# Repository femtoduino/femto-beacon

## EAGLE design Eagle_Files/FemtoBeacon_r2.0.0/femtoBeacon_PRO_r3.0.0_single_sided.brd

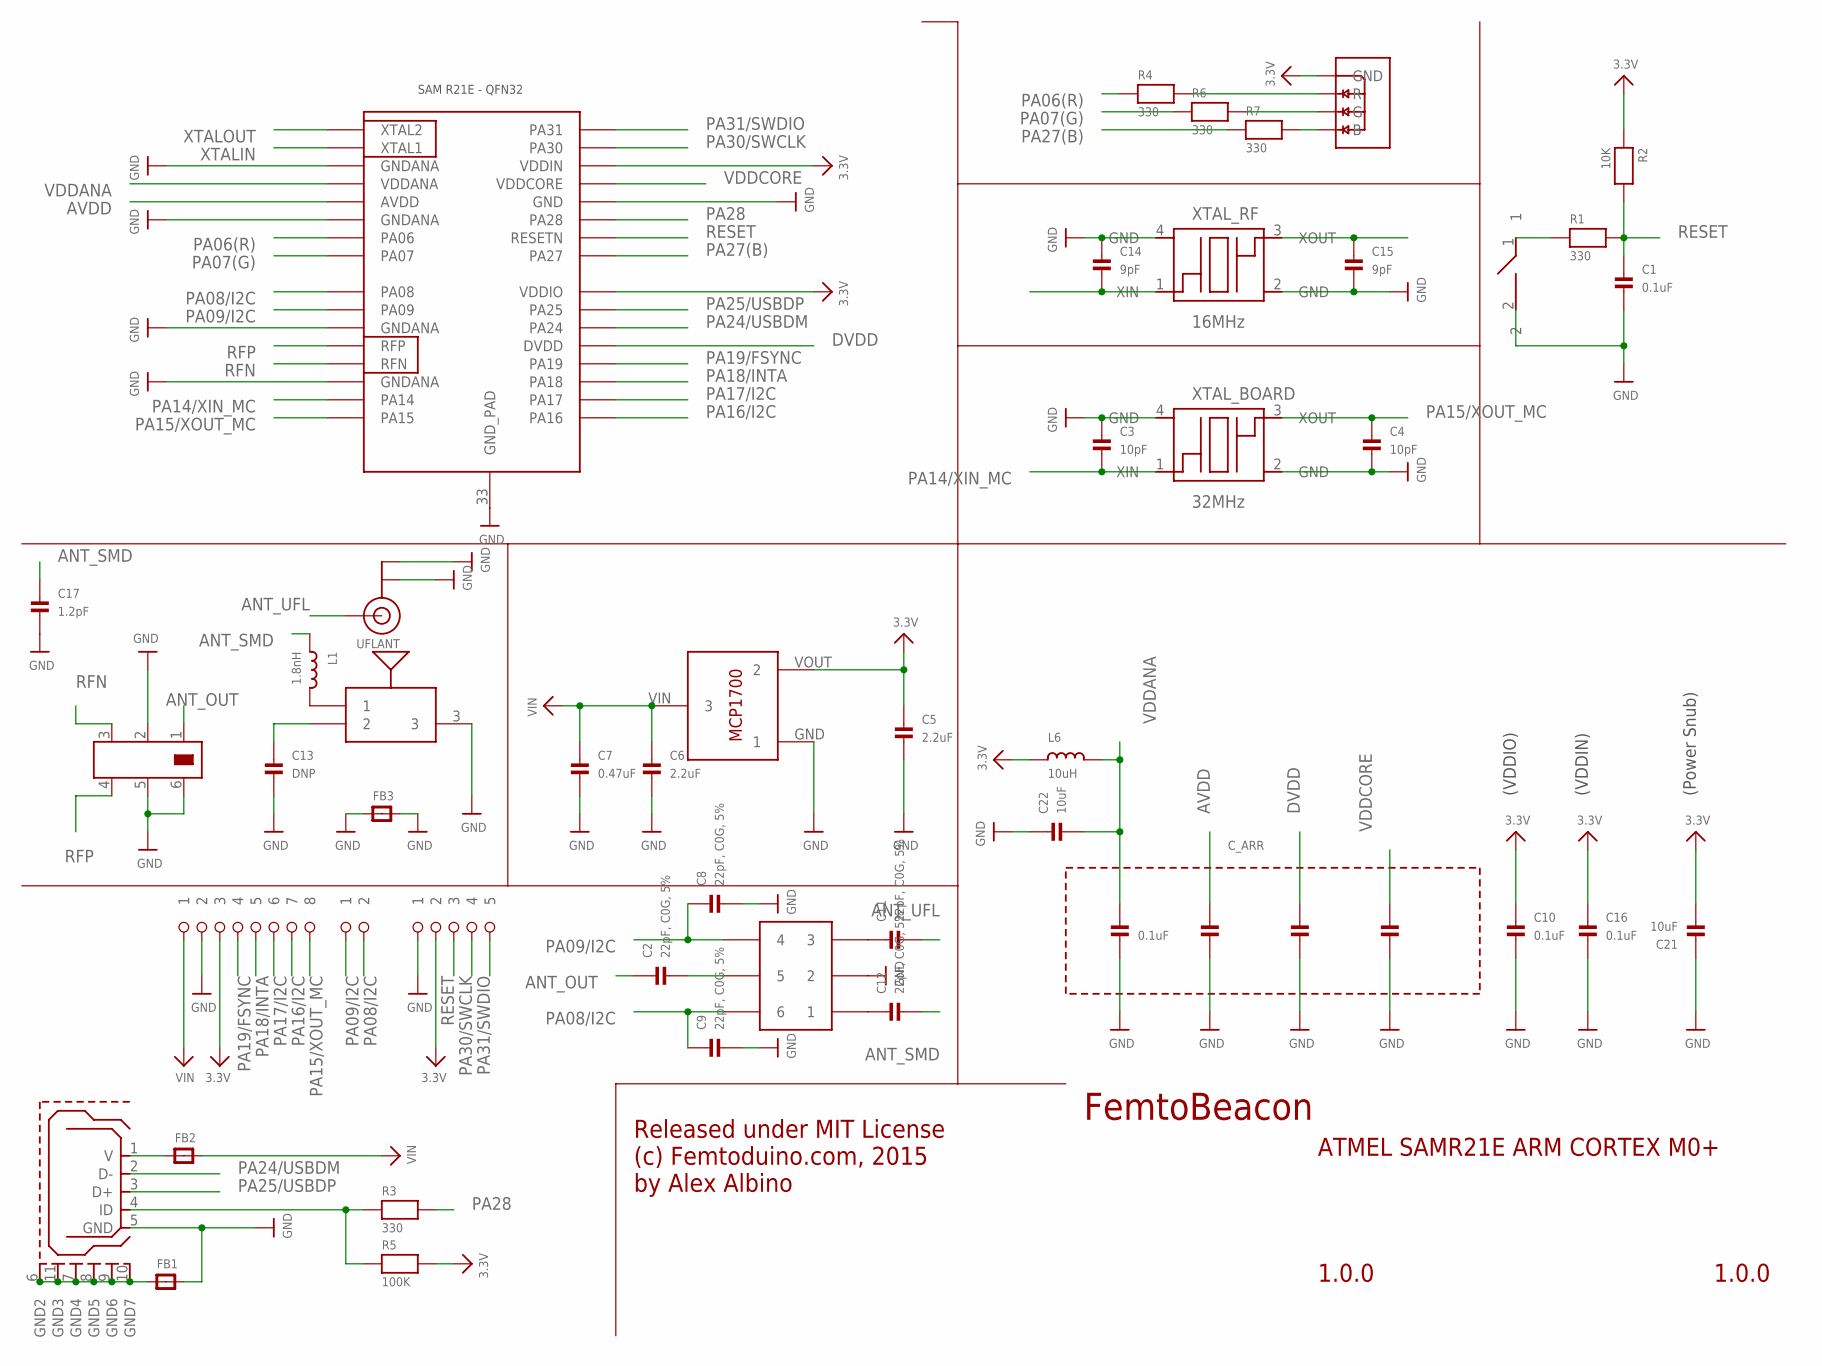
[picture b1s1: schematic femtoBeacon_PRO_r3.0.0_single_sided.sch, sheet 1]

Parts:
ASWITCH: AS222-92LF
BALUN: JOHANSON_2450BM15A0015E; 0805_BALUN
BTN_RESET: DNP; SPST_SMD
C1, C10, C16: 0.1uF; _0402MP; DIGIKEY_PART 490-3194-1-ND
C2, C8, C9, C11, C12: 22pF, C0G, 5%; _0402MP; DIGIKEY_PART 490-3194-1-ND
C3, C4: 10pF; _0402MP; DIGIKEY_PART 490-3194-1-ND
C5, C6: 2.2uF; _0402MP
C7: 0.47uF; _0402MP
C13: DNP; _0402MP; DIGIKEY_PART 490-3194-1-ND
C14, C15: 9pF; _0402MP; DIGIKEY_PART 490-3194-1-ND
C17: 1.2pF; _0402MP
C21, C22: 10uF; _0402MP
C_ARR: 0.1uF; CAPACITOR_ARRAY_1206_MONO_1X4
FB1, FB2, FB3: FERRITE_0603MP; _0603MP
IC: ATSAMR21E18A-MUT; QFN32
L1: 1.8nH; _0603MP
L6: 10uH; _0603MP
LDO_VREG: MCP1700T-3302E/TT
R1, R3, R4, R6, R7: 330; _0402MP
R2: 10K; _0402MP
R5: 100K; _0402MP
RGBLED: LRTB_R48G
SMDANT: PULSE_ANT_2.4GHZ; ANT_BAR
U$5: 1X8_ROUND
U$9: 1X2_ROUND
U$10: 1X5_ROUND
UFLANT: ANTENNA_U.FL; U.FL
USB: USB_MICROB; USB_MICROB_PACKAGE
XTAL_BOARD: 32MHz; FA-128
XTAL_RF: 16MHz; TSX-3225

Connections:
3.3V: C5.1, C10.1, C16.1, C21.2, IC.24 (VDDIO), IC.30 (VDDIN), L6.1, LDO_VREG.VOUT (2), R2.1, R5.2, RGBLED.1 (GND), U$5.P$3 (3), U$10.P$2 (2); also elsewhere on the board
ANT_OUT: BALUN.1, C2.1
ANT_SMD: C12.2, C17.1, L1.1
ANT_UFL: C11.2, UFLANT.3 (SIGNAL)
AVDD: C_ARR.3, IC.5 (AVDD)
DVDD: C_ARR.5, IC.21 (DVDD)
GND: ASWITCH.PIN2 (2), BALUN.2, BALUN.5, BALUN.6, BTN_RESET.2, C1.2, C3.1, C4.2, C5.2, C6.2, C7.2, C8.2, C9.2, C10.2, C13.2, C14.1, C15.2, C16.2, C17.2, C21.1, C22.1, C_ARR.2, C_ARR.4, C_ARR.6, C_ARR.8, FB1.2, FB3.1, FB3.2, IC.3 (GNDANA), IC.6 (GNDANA), IC.11 (GNDANA), IC.14 (GNDANA), IC.28 (GND), IC.33 (GND_PAD), LDO_VREG.GND (1), SMDANT.3, U$5.P$2 (2), U$10.P$1 (1), UFLANT.1 (GND), UFLANT.2 (GND), USB.5 (GND), XTAL_BOARD.2 (GND), XTAL_BOARD.4 (GND), XTAL_RF.2 (GND), XTAL_RF.4 (GND); also elsewhere on the board
unnamed: L1.2, SMDANT.1
unnamed: C13.1, SMDANT.2
unnamed: ASWITCH.PIN5 (5), C2.2
unnamed: FB1.1, USB.6 (GND2), USB.7 (GND4), USB.8 (GND5), USB.9 (GND6), USB.10 (GND7), USB.11 (GND3)
unnamed: R3.1, R5.1, USB.4 (ID)
unnamed: FB2.1, USB.1 (V)
unnamed: R6.2, RGBLED.3 (G)
unnamed: R7.2, RGBLED.4 (B)
unnamed: ASWITCH.PIN3 (3), C11.1
unnamed: ASWITCH.PIN1 (1), C12.1
unnamed: R4.2, RGBLED.2 (R)
unnamed: BTN_RESET.1, R1.1
PA06(R): IC.7 (PA06), R4.1
PA07(G): IC.8 (PA07), R6.1
PA08/I2C: ASWITCH.PIN6 (6), C9.1, IC.9 (PA08), U$9.P$2 (2)
PA09/I2C: ASWITCH.PIN4 (4), C8.1, IC.10 (PA09), U$9.P$1 (1)
PA14/XIN_MC: C3.2, IC.15 (PA14), XTAL_BOARD.1 (XIN)
PA15/XOUT_MC: C4.1, IC.16 (PA15), U$5.P$8 (8), XTAL_BOARD.3 (XOUT)
PA16/I2C: IC.17 (PA16), U$5.P$7 (7); also elsewhere on the board
PA17/I2C: IC.18 (PA17), U$5.P$6 (6); also elsewhere on the board
PA18/INTA: IC.19 (PA18), U$5.P$5 (5); also elsewhere on the board
PA19/FSYNC: IC.20 (PA19), U$5.P$4 (4); also elsewhere on the board
PA24/USBDM: IC.22 (PA24), USB.2 (D-)
PA25/USBDP: IC.23 (PA25), USB.3 (D+)
PA27(B): IC.25 (PA27), R7.1
PA28: IC.27 (PA28), R3.2
PA30/SWCLK: IC.31 (PA30), U$10.P$4 (4)
PA31/SWDIO: IC.32 (PA31), U$10.P$5 (5)
RESET: C1.1, IC.26 (RESETN), R1.2, R2.2, U$10.P$3 (3)
RFN: BALUN.3, IC.13 (RFN)
RFP: BALUN.4, IC.12 (RFP)
VDDANA: C22.2, C_ARR.1, IC.4 (VDDANA), L6.2
VDDCORE: C_ARR.7, IC.29 (VDDCORE)
VIN: C6.1, C7.1, FB2.2, LDO_VREG.VIN (3), U$5.P$1 (1)
XTALIN: C14.2, IC.2 (XTAL1), XTAL_RF.1 (XIN)
XTALOUT: C15.1, IC.1 (XTAL2), XTAL_RF.3 (XOUT)

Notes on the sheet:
FemtoBeacon
1.0.0
ATMEL SAMR21E ARM CORTEX M0+
Released under MIT License (c) Femtoduino.com, 2015 by Alex Albino
(Power Snub)
(VDDIO)
(VDDIN)

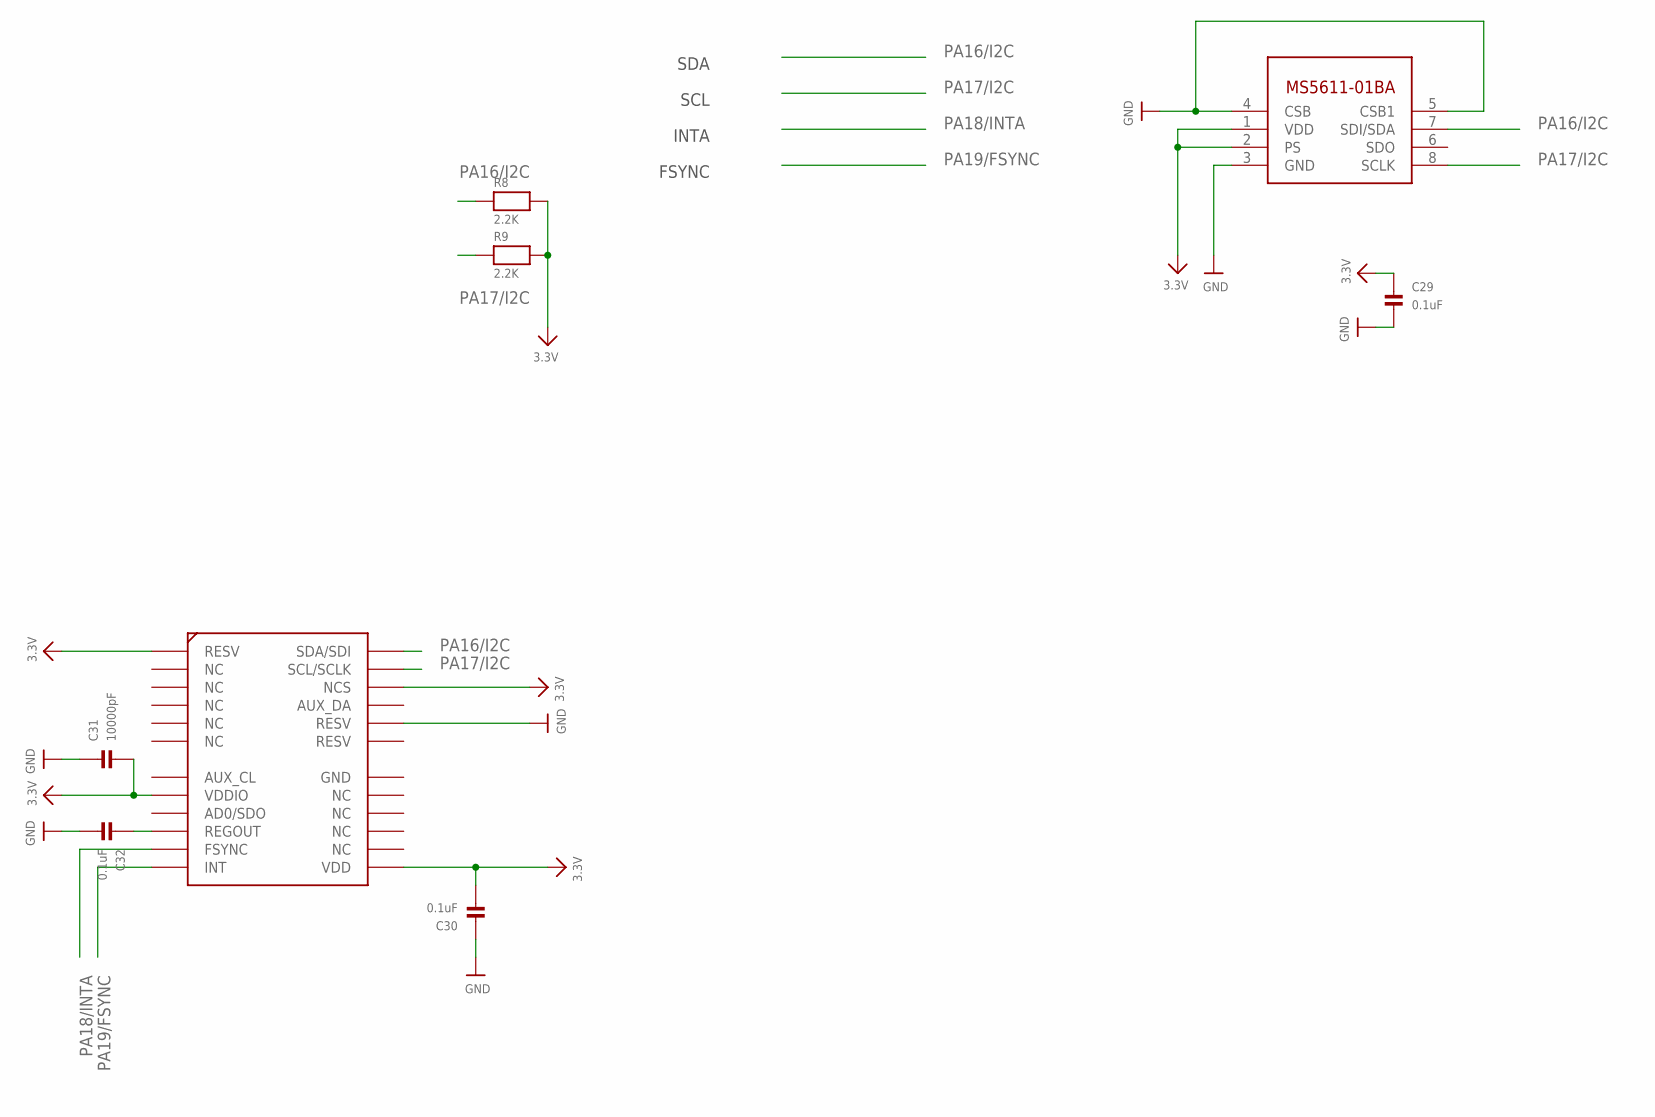
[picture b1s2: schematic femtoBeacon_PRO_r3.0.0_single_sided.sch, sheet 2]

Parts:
BARO: MS5611-01BA03
C29, C30, C32: 0.1uF; _0402MP; DIGIKEY_PART 490-3194-1-ND
C31: 10000pF; _0402MP; DIGIKEY_PART 490-3194-1-ND
IMU: MPU-9250; QFN_3X3MM
R8, R9: 2.2K; _0402MP

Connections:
3.3V: BARO.1 (VDD), BARO.2 (PS), C29.1, C30.2, C31.2, IMU.P$1 (RESV), IMU.P$8 (VDDIO), IMU.P$13 (VDD), IMU.P$22 (NCS), R8.2, R9.2; also elsewhere on the board
GND: BARO.3 (GND), BARO.4 (CSB), BARO.5 (CSB1), C29.2, C30.1, C31.1, C32.2, IMU.P$20 (RESV); also elsewhere on the board
unnamed: C32.1, IMU.P$10 (REGOUT)
PA16/I2C: BARO.7 (SDI/SDA), IMU.P$24 (SDA/SDI), R8.1; also elsewhere on the board
PA17/I2C: BARO.8 (SCLK), IMU.P$23 (SCL/SCLK), R9.1; also elsewhere on the board
PA18/INTA: IMU.P$11 (FSYNC); also elsewhere on the board
PA19/FSYNC: IMU.P$12 (INT); also elsewhere on the board

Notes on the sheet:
SDA
SCL
INTA
FSYNC

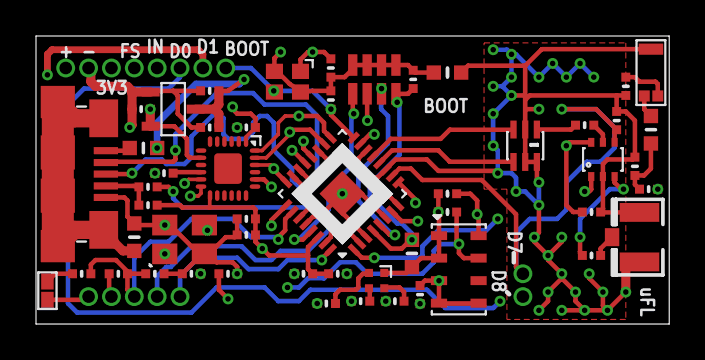
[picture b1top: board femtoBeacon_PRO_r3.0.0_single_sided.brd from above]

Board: 4 copper layers, 35.2 x 16.0 mm, 54 parts (0 on the bottom side), 44 nets.

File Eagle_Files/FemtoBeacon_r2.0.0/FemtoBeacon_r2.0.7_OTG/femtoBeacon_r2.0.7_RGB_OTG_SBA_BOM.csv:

##########################################################################
       Name: Placement Bill of Materials Generator

    Version: 4 (2-sided, top)
         By: Small Batch Assembly
        URL: www.smallbatchassembly.com
 SourceFile: femtoBeacon_r2.0.7_RGB_OTG.brd
   DateTime: 11/24/17 7:52 PM
      Units: inches
##########################################################################
REF,PACKAGE,VALUE,X,Y,ROTATION,
ANT_SMD   , 0479480001            , 0479480001     , 0.2137, 0.5543, 180.0
BALUN   , 0805_BALUN            , JOHANSON_2450BM15A0015E     , 0.3937, 0.5770, 270.0
BTN   , SPST_SMD            , DNP     , 0.8398, 0.3440, 270.0
C1   , PART            , 0.1uF     , 0.7968, 0.3190, 270.0
C2   , PART            , 0.1uF     , 0.6077, 0.4490, 0.0
C5   , _0402MP            , 2.2uF     , 0.7167, 0.3200, 180.0
C6   , _0402MP            , 2.2uF     , 0.5987, 0.3510, 180.0
C7   , PART            , 0.47uF     , 0.6047, 0.2910, 180.0
C8   , PART            , 0.1uF     , 0.7687, 0.7430, 180.0
C9   , PART            , 0.1uF     , 0.7318, 0.6870, 0.0
C10   , PART            , 0.1uF     , 0.5397, 0.3240, 180.0
C11   , _0402MP            , 1.2pF     , 0.3850, 0.4650, 0.0
C12   , PART            , 22pF     , 0.3937, 0.6550, 180.0
C13   , PART            , DNP     , 0.3900, 0.4350, 0.0
C14   , PART            , 9pF     , 0.5277, 0.7920, 270.0
C15   , PART            , 9pF     , 0.7167, 0.7550, 270.0
C16   , PART            , 0.1uF     , 0.6067, 0.3975, 0.0
C17   , PART            , 0.1uF     , 0.7587, 0.7160, 180.0
C21   , _0402MP            , 10uF     , 0.4267, 0.7890, 180.0
C22   , _0402MP            , 10uF     , 0.4667, 0.7560, 0.0
C31   , PART            , 10nF     , 0.5357, 0.2940, 0.0
FB1   , _0603MP            , Ferrite     , 0.7347, 0.3970, 180.0
FID1   , FIDUCIAL_1MM            , FIDUCIAL     , 0.1000, 0.3000, 0.0
FID2   , FIDUCIAL_1MM            , FIDUCIAL     , 0.1000, 0.8000, 0.0
FID3   , FIDUCIAL_1MM            , FIDUCIAL     , 1.2000, 0.8000, 0.0
IC   , QFN32            , ATSAMR21E18A-MUT     , 0.5861, 0.5907, 270.0
L1   , _0603MP            , 1.8nH     , 0.3300, 0.4650, 270.0
L6   , _0603MP            , 10uH     , 0.4317, 0.7190, 0.0
LDO_VREG   , MCP1700T-3302E/TT            , MCP1700T-3302E/TT     , 0.6581, 0.3211, 90.0
R1   , PART            , 330     , 0.7767, 0.3600, 180.0
R2   , PART            , 10K     , 0.7637, 0.3190, 270.0
R4   , PART            , 330     , 0.7760, 0.7880, 0.0
R5   , PART            , 330     , 0.7350, 0.5600, 0.0
R6   , PART            , 330     , 0.7700, 0.8150, 0.0
R7   , PART            , 330     , 0.7800, 0.8450, 0.0
R10   , PART            , 100K     , 0.7750, 0.6140, 90.0
RGBLED   , LRTB_R48G            , LRTB_R48G     , 0.8300, 0.7950, 270.0
USB   , USB_MICROB_PACKAGE            , USB_MICROB     , 0.8764, 0.5550, 90.0
XOSCRF   , TSX-3225            , 16MHz     , 0.6240, 0.7825, 0.0

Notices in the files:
parts and their libraries:
microbuilder: This work is placed in the public domain, and may be freely used for commercial and non-commercial work with the following conditions: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
